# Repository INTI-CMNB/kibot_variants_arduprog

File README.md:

# KiBot variants example

This is an example of how to use variants with [KiBot](https://github.com/INTI-CMNB/KiBot).

## Index

* [Definition](#Definition)
* [Implementation](#Implementation)
* [Example](#Example)
* [**Results**](#Results)
  * [Schematic PDF](#Schematic-PDF)
  * [Bill of Materials](#Bill-of-Materials)
  * [PCB PDF](#PCB-PDF)
  * [Gerbers](#Gerbers)
  * [Position](#Position)
  * [3D Model](#3D-Model)
* [Changing values](#Changing-values)
* [A complete example](#A-complete-example)

# Definition

In the KiBot context a variant is what is usually known as an *assembly variant*.
So the idea is that you have **one** PCB, but various different *variants* (*flavors*) of the product.
The difference between them is which components are used.

Typical applications are:
- Optional functionality
- Support for different normatives
- Testing purposes

Currently KiBot can handle not only which components are soldered, but also different values.
The support for different values is complex and only used by a minority.
So please be patient if some use case isn't well covered, just report it.

# Implementation

To create a variant you must add specific fields to the components in the schematic.
Currently KiBot supports three methodes:

- **KiBoM style**: one field, usually named *Config*, contains information to include or exclude a component for one or more variants.
- **KiCost style**: one field assigns the component to one or more groups, you provide a regular expression to include certain groups.
- **IBoM style**: one field assigns the component to a group, you provide lists to exclude or include certain groups.

# Example

The best way to explain how to use it is using an example.
We start with an hypothetic design: the *programmer* section of the [Arduino UNO R3](https://content.arduino.cc/assets/UNO-TH_Rev3e_sch.pdf).
The schematic is the following:

This is basically an ATMega8U2 used as a bridge between USB and the Arduino UNO serial port.
So we will assume this board is useful. We'll also assume we have three possible uses:

- The full board with USB support. We'll name it **USB** variant.
- A version of the board that we want to use as a plain microcontroller. So we remove the USB. We'll name it **XTAL** variant.
- An even more modest version where we use the internal clock oscillator and we can remove the crystal. We'll name it **default** variant.

Additionally:

- In the USB version we want to remove the ICSP1 connector. We'll flash the CPU in-house and the user won't need to do it. ICPS1 will be solded for the other two variants.
- The J4 connector is completely optional. It won't be included in any variant.

The first step is to choose a variant mechanism. For this example we will use the [KiBoM](https://github.com/SchrodingersGat/KiBoM) style.
This style puts more information inside the schematic, so you need to provide less information from outside.

Now that we chose a format we must add the corresponding *tags*. We can identify four groups of components here:

- The USB components (J2, F1, R1, R2, RV1, RV2 and FB1). Used only for the **USB** variant.
- The ICSP1 connector (J5). Excluded from the **USB** variant.
- The crystal components (R3, Y1, C3, C4). Used only for the **USB** and **XTAL** variants.
- The 2x2M connector (J4). Never used.

To mark components that will be added to the board only for certain variant KiBoM uses **+VARIANT**.
And when we want to exclude a component from a variant we use **-VARIANT**.

We'll use the default *Config* field. So lets see what we'll use for each group.

- For the USB components we'll use **+USB** because these components will be used only for the **USB** variant.
- For the ICSP1 connector we'll use **-USB** because this component will be solded for all variants, except **USB**.
- Now the crystal stuff is a little bit more complex. We could use **+XTAL**, but then these components won't be included in the **USB** version.
  So what we use is **+USB,+XTAL** this makes the components available for both variants.
- The J4 case is handled in a different way. KiBoM filters removes any component mentioning the **DNF** word in the config. So we can just use it.

Now that we know what to use we'll add the *Config* field to the mentioned components.
To make it faster we can add it to one component, lets say to J4, and then use the *Tools -> Edit symbol fields* menu option.
Here is what we should have in the *Config* field:

This is all we need to add to the schematic. Now is time to configure KiBot.

If you don't know about the KiBot file format you could be interested in reading the following [explanation](https://github.com/INTI-CMNB/KiBot/blob/master/docs/KiPlotYAML.md).
YAML files are self explanatory, so perhaps you can go on even without knowing about the format.

Ok, now we have to define the three variants we mentioned before: **USB**, **XTAL** and **default**.
All variants will be put in a section named **variants**. So we'll create a list of items, each item is a variant definition.
Lets start with the simplest: **default**. Here is what we use:

```yaml
variants:
  - name: 'default'
    comment: 'Minimal PCB no USB'
    type: kibom
```

This is the section **variants** and its first item. The name is **default** and we added a comment to remmember what this variant is.
We also define the type as **kibom**, what we called *style*.

Now lets go for the second, here we add:

```yaml
  - name: 'USB'
    comment: 'Full board'
    type: kibom
    file_id: _USB
    variant: USB
```

You'll notice two new attributes: `file_id` and `variant`. The first is what we'll add to the names of the files in order to distinguish from the **default**.
And the second ... well this is just the *tag* we used to mark **USB** components.

You should be able to figure out how to define the third variant, here we go:

```yaml
  - name: 'XTAL'
    comment: 'No USB, but crystal included'
    type: kibom
    file_id: _XTAL
    variant: XTAL
```

A little bit long, but simple. Here is all together:

```yaml
variants:
  - name: 'default'
    comment: 'Minimal PCB no USB'
    type: kibom

  - name: 'USB'
    comment: 'Full board'
    type: kibom
    file_id: _USB
    variant: USB

  - name: 'XTAL'
    comment: 'No USB, but crystal included'
    type: kibom
    file_id: _XTAL
    variant: XTAL
```

This is all we need to define the variants. Of course our config file must define what to do with the variants.
But this document is about the variants, we won't focuse on the rest.
You can see the whole configuration file [here](ardu_prog.kibot.yaml).

What now? How can we tell KiBot what variant to use?
There are three methodes:

1. Use the `variant` option for an specific output.
2. Select a default variant to be used by all outputs that doesn't specify a variant.
3. Same as above but from the command line.

The simplest way is the third. In this case we just need to add `-g variant=NAME` to the command line.
Lets say we have a copy of the repo containing this example and we want to generate the BoM.
In our example the HTML BoM output is named `bom_html` so we can just run:

```bash
kibot -s run_erc,run_drc -d Result bom_html
```

This will create `Result/BoM/t1-bom.html`. To generate the BoM for the **USB** variant we can use:

```bash
kibot -s run_erc,run_drc -d USB -g variant=USB bom_html
```

And we'll get a different BoM in `USB/BoM/t1-bom_USB.html`.

The CI/CD workflow for this repo runs the ERC and DRC checks and then generates all the configured outputs for the three variants.
The commands used are approximately these:

```bash
kibot -d Generated -s run_drc -i
kibot -d Generated -s run_erc -i
kibot -d Generated/default -g variant=default -s run_erc,run_drc
kibot -d Generated/USB -g variant=USB -s run_erc,run_drc
kibot -d Generated/XTAL -g variant=XTAL -s run_erc,run_drc
```

The first two are the checks, no output generated. The other three skips the checks and generates all outputs for each variant.
All files are stored in the `Generated` folder.

# Results

Here is what we get, you can download the results obtained on GitHub CI/CD Actions from [here](https://github.com/INTI-CMNB/kibot_variants_arduprog/actions/runs/4584580459).
Click on the images to get a larger image or the generated document.

## Schematic PDF

Excluded components are marked with a cross:

- Default variant

- XTAL variant

- USB variant

## Bill of Materials

Excluded components are listed as DNF in a separated list. Note we could also remove them.

- Default variant

- XTAL variant

- USB variant

The XLSX files contain the same information, arranged a little bit different, here is the USB variant:

## PCB PDF

Excluded components are marked with a cross in the *.Fab layer. Their solder paste and adhesive glue is removed from *.Paste and *.Adhes.
The following PDFs were gnerated including F.Fab, F.Paste, F.Adhes and Dwgs.User:

- Default variant

- XTAL variant

- USB variant

## Gerbers

Excluded components are marked with a cross in the *.Fab layer. Their solder paste and adhesive glue is removed from *.Paste and *.Adhes:

- Default variant

- XTAL variant

- USB variant

## Position

Here only the fitted components are included in the pick and place file:

- Default variant
```
### Module positions - created on Thu 10 Sep 2020 20:10:57  ###
### Printed by KiBot
## Unit = mm, Angle = deg.
## Side : both
# Ref   Val                  Package                                     PosX       PosY       Rot        Side
C1     47uF                 CP_Elec_8x10                                130.8354   -94.8944   270.0000   top
C2     100nF                C_0805_2012Metric                           123.0000   -90.9000   0.0000     top
C5     1uF                  C_0805_2012Metric                           163.3220   -89.1540   270.0000   top
C6     100nF                C_0805_2012Metric                           162.3822   -82.0674   90.0000    top
C7     100nF                C_0805_2012Metric                           153.9748   -78.8670   0.0000     top
C8     100nF                C_0805_2012Metric                           144.7546   -78.9686   90.0000    top
D1     CD1206-S01575        D_1206_3216Metric                           162.8140   -96.7740   90.0000    top
D2     LED                  LED_0805_2012Metric                         147.3200   -74.9500   90.0000    top
D3     LED                  LED_0805_2012Metric                         144.7800   -74.9500   90.0000    top
J1     Barrel_Jack_Switch   BarrelJack_CLIFF_FC681465S_SMT_Horizontal   126.1000   -81.2000   0.0000     top
R4     10K                  R_0805_2012Metric                           159.0040   -95.7580   90.0000    top
R5     1K                   R_0805_2012Metric                           144.7546   -82.8040   270.0000   top
R6     1K                   R_0805_2012Metric                           147.3200   -70.1748   270.0000   top
R7     1K                   R_0805_2012Metric                           144.7800   -70.1748   270.0000   top
U1     ATmega8U2-AU         TQFP-32_7x7mm_P0.8mm                        154.4320   -85.8520   270.0000   top
## End
```
- XTAL variant
```
### Module positions - created on Thu 10 Sep 2020 20:11:59  ###
### Printed by KiBot
## Unit = mm, Angle = deg.
## Side : both
# Ref   Val                  Package                                     PosX       PosY       Rot        Side
C1     47uF                 CP_Elec_8x10                                130.8354   -94.8944   270.0000   top
C2     100nF                C_0805_2012Metric                           123.0000   -90.9000   0.0000     top
C3     22pF                 C_0805_2012Metric                           162.2600   -75.1160   270.0000   top
C4     22pF                 C_0805_2012Metric                           155.9100   -75.1160   270.0000   top
C5     1uF                  C_0805_2012Metric                           163.3220   -89.1540   270.0000   top
C6     100nF                C_0805_2012Metric                           162.3822   -82.0674   90.0000    top
C7     100nF                C_0805_2012Metric                           153.9748   -78.8670   0.0000     top
C8     100nF                C_0805_2012Metric                           144.7546   -78.9686   90.0000    top
D1     CD1206-S01575        D_1206_3216Metric                           162.8140   -96.7740   90.0000    top
D2     LED                  LED_0805_2012Metric                         147.3200   -74.9500   90.0000    top
D3     LED                  LED_0805_2012Metric                         144.7800   -74.9500   90.0000    top
J1     Barrel_Jack_Switch   BarrelJack_CLIFF_FC681465S_SMT_Horizontal   126.1000   -81.2000   0.0000     top
R3     1M                   R_0805_2012Metric                           158.9580   -75.8780   180.0000   top
R4     10K                  R_0805_2012Metric                           159.0040   -95.7580   90.0000    top
R5     1K                   R_0805_2012Metric                           144.7546   -82.8040   270.0000   top
R6     1K                   R_0805_2012Metric                           147.3200   -70.1748   270.0000   top
R7     1K                   R_0805_2012Metric                           144.7800   -70.1748   270.0000   top
U1     ATmega8U2-AU         TQFP-32_7x7mm_P0.8mm                        154.4320   -85.8520   270.0000   top
Y1     16MHz                Crystal_SMD_Abracon_ABM3-2Pin_5.0x3.2mm     158.9278   -70.0278   180.0000   top
## End
```
- USB variant
```
### Module positions - created on Thu 10 Sep 2020 20:11:27  ###
### Printed by KiBot
## Unit = mm, Angle = deg.
## Side : both
# Ref   Val                  Package                                     PosX       PosY       Rot        Side
C1      47uF                 CP_Elec_8x10                                130.8354   -94.8944   270.0000   top
C2      100nF                C_0805_2012Metric                           123.0000   -90.9000   0.0000     top
C3      22pF                 C_0805_2012Metric                           162.2600   -75.1160   270.0000   top
C4      22pF                 C_0805_2012Metric                           155.9100   -75.1160   270.0000   top
C5      1uF                  C_0805_2012Metric                           163.3220   -89.1540   270.0000   top
C6      100nF                C_0805_2012Metric                           162.3822   -82.0674   90.0000    top
C7      100nF                C_0805_2012Metric                           153.9748   -78.8670   0.0000     top
C8      100nF                C_0805_2012Metric                           144.7546   -78.9686   90.0000    top
D1      CD1206-S01575        D_1206_3216Metric                           162.8140   -96.7740   90.0000    top
D2      LED                  LED_0805_2012Metric                         147.3200   -74.9500   90.0000    top
D3      LED                  LED_0805_2012Metric                         144.7800   -74.9500   90.0000    top
F1      MF-MSMF050-2         R_1812_4532Metric                           167.8940   -77.2160   0.0000     top
FB1     BLM21PG221SN1D       R_0805_2012Metric                           167.8940   -90.6780   180.0000   top
J1      Barrel_Jack_Switch   BarrelJack_CLIFF_FC681465S_SMT_Horizontal   126.1000   -81.2000   0.0000     top
R1      22R                  R_0805_2012Metric                           166.3700   -86.1060   0.0000     top
R2      22R                  R_0805_2012Metric                           166.3700   -83.8200   0.0000     top
R3      1M                   R_0805_2012Metric                           158.9580   -75.8780   180.0000   top
R4      10K                  R_0805_2012Metric                           159.0040   -95.7580   90.0000    top
R5      1K                   R_0805_2012Metric                           144.7546   -82.8040   270.0000   top
R6      1K                   R_0805_2012Metric                           147.3200   -70.1748   270.0000   top
R7      1K                   R_0805_2012Metric                           144.7800   -70.1748   270.0000   top
RV1     CG0603MLC-05E        R_0603_1608Metric                           170.4340   -87.3505   270.0000   top
RV2     CG0603MLC-05E        R_0603_1608Metric                           170.4340   -82.3214   90.0000    top
U1      ATmega8U2-AU         TQFP-32_7x7mm_P0.8mm                        154.4320   -85.8520   270.0000   top
Y1      16MHz                Crystal_SMD_Abracon_ABM3-2Pin_5.0x3.2mm     158.9278   -70.0278   180.0000   top
## End
```

## 3D Model

Excluded components are removed from the 3D model (STEP file, 3D Viewer render and Blender export):

- Default variant (click to enlarge)

- XTAL variant (click to enlarge)

- USB variant (click to enlarge)

# Changing values

Variants can also affect any of the component fields. In order to overwrite one field value when a variant is selected you must define a field named `VARIANT:FIELD`.
The value for this field will replace the value of the regular `FIELD` when the `VARIANT` is in use.

Here is an example, if you have a resistor with a value of 1k and you want this value to change to 2k2 when the `test` variant is in use you just need to define a field named `test:value` and assign `2k2` to this field.

To enable it you just need to add a `pre_transform` filter of the type `var_rename` to the variant performing the transformation. Suppose you have the following variants:

```yaml
variants:
  - name: 'production'
    comment: 'Production variant'
    type: kibom
    file_id: '_(PROD)'
    variant: PROD

  - name: 'development'
    comment: 'Development variant'
    type: kibom
    file_id: '_(DEV)'
    variant: DEV
```

And you want to both apply such a transformation you can define:

```yaml
filters:
  - name: 'Variant rename'
    type: var_rename
    separator: ':'
    variant_to_value: true

variants:
  - name: 'production'
    comment: 'Production variant'
    type: kibom
    file_id: '_(PROD)'
    variant: PROD
    pre_transform: 'Variant rename'

  - name: 'development'
    comment: 'Development variant'
    type: kibom
    file_id: '_(DEV)'
    variant: DEV
    pre_transform: 'Variant rename'
```

The `separator` option controls which character is used to separate the `VARIANT` and the `FIELD` in the field name.

The `variant_to_value` enables the conversion from fields named `VARIANT` to the component value when the variant is in use.

To make things simpler you can use an internally defined filter called `_var_rename`. This is a `var_rename` filter with `:` as separator and `variant_to_value` disabled. Using it the configuration is simpler:

```yaml
variants:
  - name: 'production'
    comment: 'Production variant'
    type: kibom
    file_id: '_(PROD)'
    variant: PROD
    pre_transform: '_var_rename'

  - name: 'development'
    comment: 'Development variant'
    type: kibom
    file_id: '_(DEV)'
    variant: DEV
    pre_transform: '_var_rename'
```

# A complete example

The configuration file used in this example can be found [here](https://github.com/INTI-CMNB/kibot_variants_arduprog/blob/master/ardu_prog.kibot.yaml).

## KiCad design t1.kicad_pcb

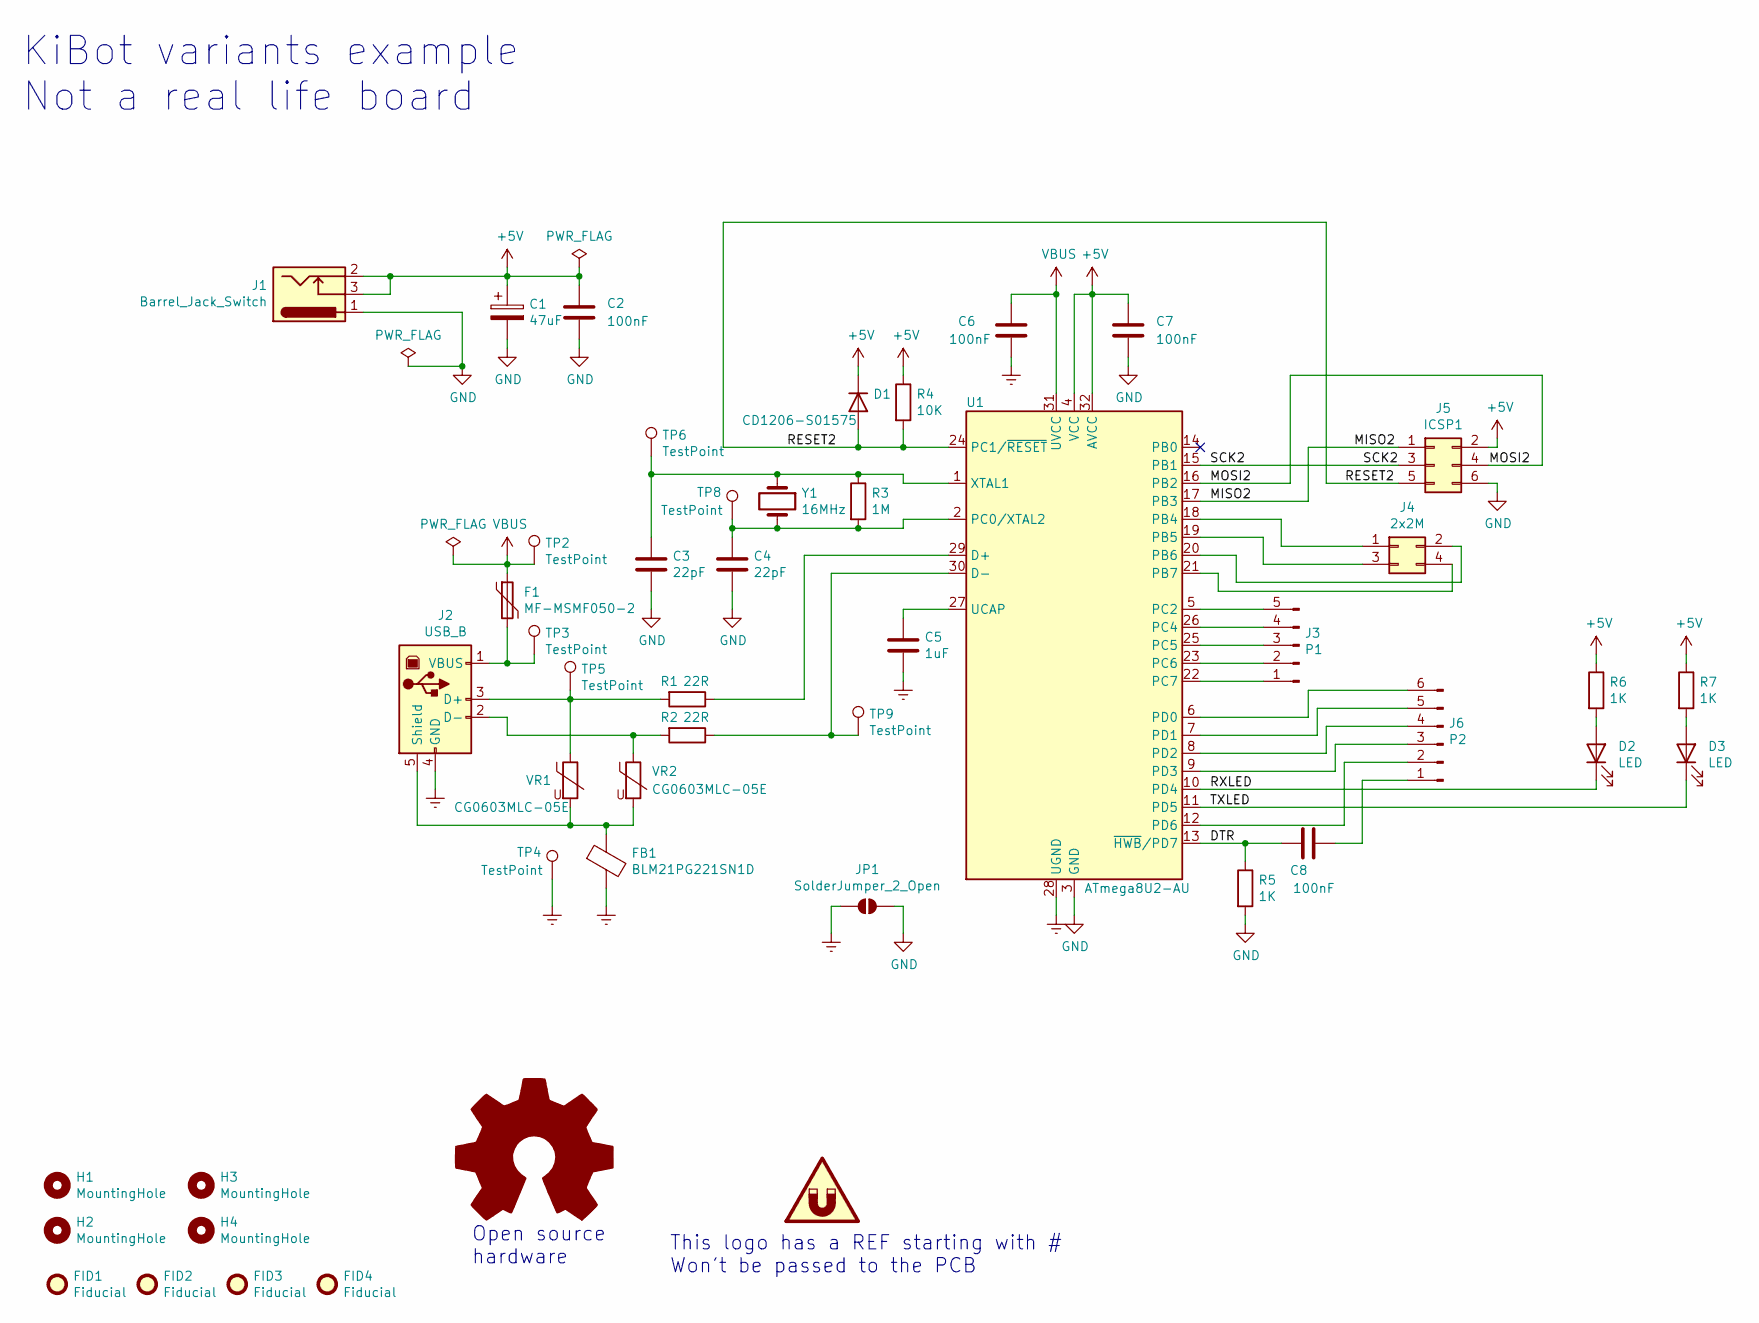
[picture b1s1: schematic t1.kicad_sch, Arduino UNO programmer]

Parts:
C1: 47uF; CP_Elec_8x10
C2, C6, C7, C8: 100nF; C_0805_2012Metric
C3, C4: 22pF; C_0805_2012Metric
C5: 1uF; C_0805_2012Metric
D1: CD1206-S01575; D_1206_3216Metric
D2, D3: LED; LED_0805_2012Metric
F1: MF-MSMF050-2; R_1812_4532Metric
FB1: BLM21PG221SN1D; R_0805_2012Metric
FID1, FID2, FID3, FID4: Fiducial; Fiducial_0.75mm_Mask1.5mm
H1, H2, H3, H4: MountingHole; MountingHole_2.7mm_M2.5
J1: Barrel_Jack_Switch; BarrelJack_CLIFF_FC681465S_SMT_Horizontal
J2: USB_B; USB_B_Lumberg_2411_02_Horizontal
J3: P1; PinHeader_1x05_P2.54mm_Vertical
J4: 2x2M; PinHeader_2x02_P2.54mm_Vertical
J5: ICSP1; PinHeader_2x03_P2.54mm_Vertical
J6: P2; PinHeader_1x06_P2.54mm_Vertical
JP1: SolderJumper_2_Open; SolderJumper-2_P1.3mm_Open_RoundedPad1.0x1.5mm
LOGO1: Logo_Open_Hardware_Large; OSHW-Logo_11.4x12mm_SilkScreen
R1, R2: 22R; R_0805_2012Metric
R3: 1M; R_0805_2012Metric
R4: 10K; R_0805_2012Metric
R5, R6, R7: 1K; R_0805_2012Metric
TP2, TP3, TP4, TP5, TP6, TP8, TP9: TestPoint; TestPoint_Pad_D1.0mm
U1: ATmega8U2-AU; TQFP-32_7x7mm_P0.8mm
VR1, VR2: CG0603MLC-05E; R_0603_1608Metric
Y1: 16MHz; Crystal_SMD_Abracon_ABM3-2Pin_5.0x3.2mm

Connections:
+5V: C1.1, C2.1, C7.1, D1.1 (K), J1.2, J1.3, J5.2, R4.1, R6.1, R7.1, U1.4 (VCC), U1.32 (AVCC)
/DTR: C8.1, R5.1, U1.13 (~HWB/PD7)
/MISO2: J5.1, U1.17 (PB3)
/MOSI2: J5.4, U1.16 (PB2)
/RESET2: D1.2 (A), J5.5, R4.2, U1.24 (PC1/~RESET)
/RXLED: D2.1 (K), U1.10 (PD4)
/SCK2: J5.3, U1.15 (PB1)
/TXLED: D3.1 (K), U1.11 (PD5)
Earth: C5.2, C6.2, FB1.2, J2.4 (GND), JP1.1 (A), TP4.1, U1.28 (UGND)
GND: C1.2, C2.2, C3.2, C4.2, C7.2, J1.1, J5.6, JP1.2 (B), R5.2, U1.3 (GND)
unnamed: D2.2 (A), R6.2
unnamed: D3.2 (A), R7.2
unnamed: J2.3 (D+), R1.2, TP5.1, VR1.1
unnamed: J2.2 (D-), R2.2, VR2.1
unnamed: FB1.1, J2.5 (Shield), VR1.2, VR2.2
unnamed: F1.2, J2.1 (VBUS), TP3.1
unnamed: J3.1, U1.22 (PC7)
unnamed: J3.2, U1.23 (PC6)
unnamed: J3.3, U1.25 (PC5)
unnamed: J3.4, U1.26 (PC4)
unnamed: J3.5, U1.5 (PC2)
unnamed: J4.1, U1.18 (PB4)
unnamed: J4.2, U1.20 (PB6)
unnamed: J4.3, U1.19 (PB5)
unnamed: J4.4, U1.21 (PB7)
unnamed: C8.2, J6.1
unnamed: J6.2, U1.12 (PD6)
unnamed: J6.3, U1.9 (PD3)
unnamed: J6.4, U1.8 (PD2)
unnamed: J6.5, U1.7 (PD1)
unnamed: J6.6, U1.6 (PD0)
unnamed: R1.1, U1.29 (D+)
unnamed: R2.1, TP9.1, U1.30 (D-)
unnamed: C4.1, R3.2, TP8.1, U1.2 (PC0/XTAL2), Y1.2
unnamed: C5.1, U1.27 (UCAP)
unnamed: C3.1, R3.1, TP6.1, U1.1 (XTAL1), Y1.1
VBUS: C6.1, F1.1, TP2.1, U1.31 (UVCC)

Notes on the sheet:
Open source hardware
This logo has a REF starting with # Won't be passed to the PCB
KiBot variants example Not a real life board

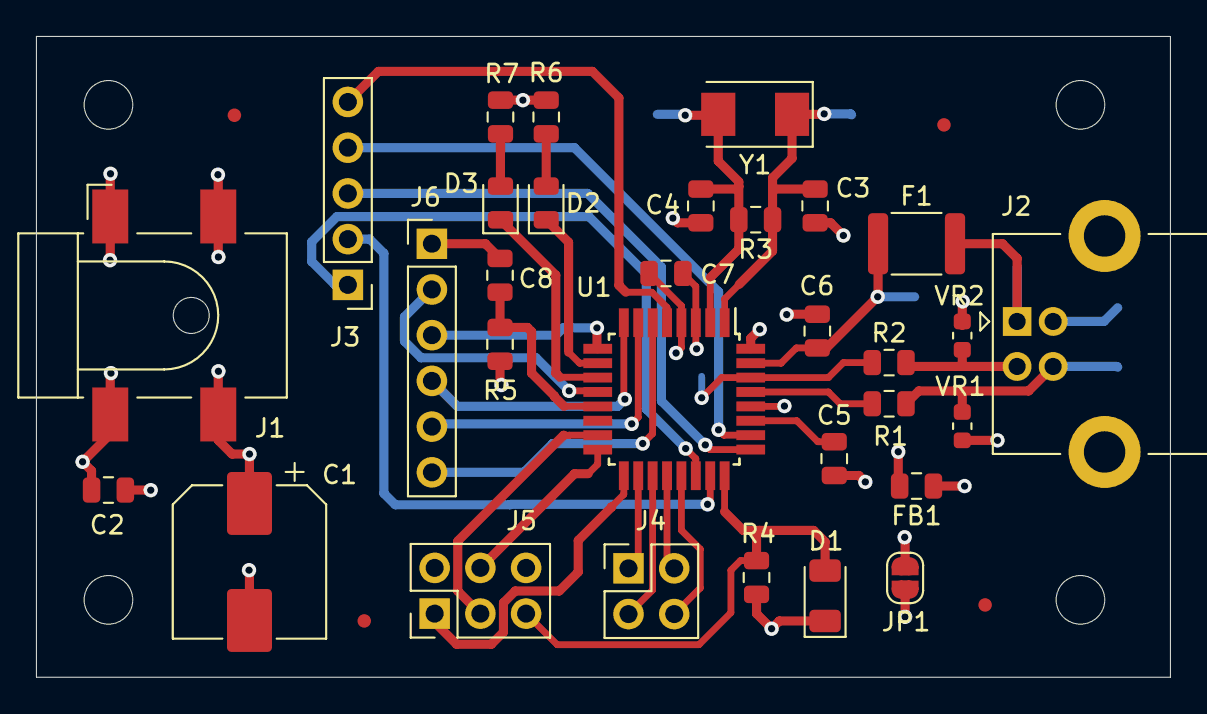
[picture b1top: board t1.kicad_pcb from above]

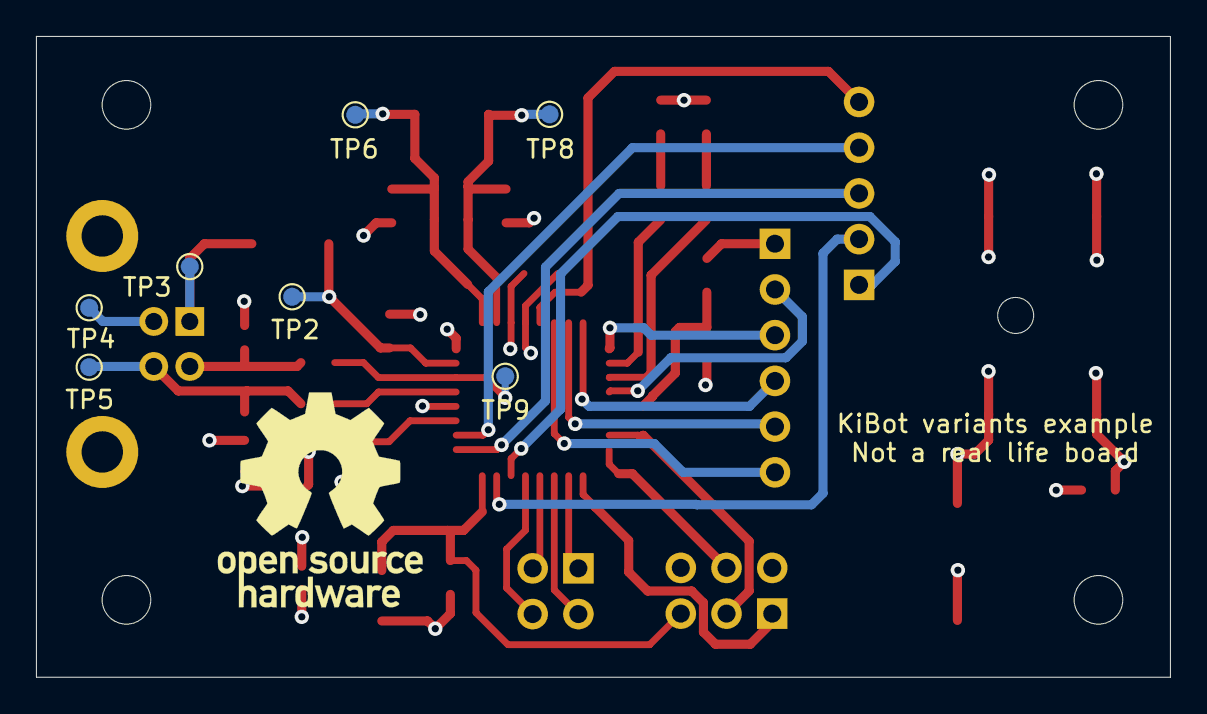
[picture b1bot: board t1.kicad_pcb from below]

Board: 4 copper layers, 63.0 x 35.6 mm, 47 parts (8 on the bottom side), 37 nets.

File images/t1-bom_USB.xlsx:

|  | KiBot variants example
 |  | Schematic: | t1 | Component Groups: | 21
 |  | Variant: | USB | Component Count: | 30
 |  | Revision: | r1 | Fitted Components: | 28
 |  | Date: | 2020-09-09 | Number of PCBs: | 1
 |  | KiCad Version: | 5.1.6+dfsg1-1~bpo10+1 | Total Components: | 28
Row | References | Quantity Per PCB | Value | Manufacturer | Manf. Part | Footprint
1 | C3 C4 | 2 | 22 pF |  |  | C_0805_2012Metric
2 | C2 C6 C7 C8 | 4 | 100 nF |  |  | C_0805_2012Metric
3 | C5 | 1 | 1 µF |  |  | C_0805_2012Metric
4 | C1 | 1 | 47 µF | Vishay Beyschlag/Draloric/BC Components | MAL215371479E3 | CP_Elec_8x10
5 | D1 | 1 | CD1206-S01575 |  |  | D_1206_3216Metric
6 | D2 D3 | 2 | LED | OSRAM Opto Semiconductors Inc. | LG R971-KN-1 | LED_0805_2012Metric
7 | F1 | 1 | MF-MSMF050-2 |  |  | R_1812_4532Metric
8 | FB1 | 1 | BLM21PG221SN1D | Murata | BLM21PG221SN1D | R_0805_2012Metric
9 | J1 | 1 | Barrel_Jack_Switch | Würth Elektronik | 694106106102 | BarrelJack_CLIFF_FC681465S_SMT_Horizontal
10 | J3 | 1 | P1 |  |  | PinHeader_1x05_P2.54mm_Vertical
11 | J6 | 1 | P2 |  |  | PinHeader_1x06_P2.54mm_Vertical
12 | J2 | 1 | USB_B | TE Connectivity AMP Connectors | 292304-1 | USB_B_Lumberg_2411_02_Horizontal
13 | R1 R2 | 2 | 22 Ω |  |  | R_0805_2012Metric
14 | R5 R6 R7 | 3 | 1 kΩ |  |  | R_0805_2012Metric
15 | R4 | 1 | 10 kΩ |  |  | R_0805_2012Metric
16 | R3 | 1 | 1 MΩ |  |  | R_0805_2012Metric
17 | RV1 RV2 | 2 | CG0603MLC-05E | Bourns Inc. | CG0603MLC-05E | R_0603_1608Metric
18 | U1 | 1 | ATmega8U2-AU |  |  | TQFP-32_7x7mm_P0.8mm
19 | Y1 | 1 | 16MHz | Abracon LLC | ABM3-16.000MHZ-B2-T | Crystal_SMD_Abracon_ABM3-2Pin_5.0x3.2mm

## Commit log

2020-09-10 Added the schematic and PCB
2020-09-10 Added all the 3D models used to this project.
2020-09-10 Added workflow to generate all data
2020-09-10 Added files needed for data generation
2020-09-10 Removed time command use, not in docker image.
2020-09-10 Added introduction and schematic
2020-09-10 Added snapshot of the Symbol Fields dialog.
2020-09-10 Added resulting schematic
2020-09-10 Added BoMs
2020-09-10 Switched to GitHub Pages.
2020-09-10 More changes to pages
2020-09-11 Added one XLSX examples.
2020-09-11 Added gerber images
2020-09-11 Added pick & place files.
2020-09-11 Changed position URLs to point to Git Pages
2020-09-11 Experimented with embedded .pos
2020-09-11 Added STEP images
2020-09-11 Added missing STEP images.
2020-09-11 Testing better index
2020-09-11 Trying with - instead of space
2020-09-11 Added more index entries
2020-09-11 Fixed links
2020-09-11 Experimenting with better title for images.
2020-09-11 Better image titles
2020-09-11 Added variable to make it easier to run a local copy of kibot
2020-09-11 Added a PDF output with F.Fab, F.Paste and F.Adhes.
2020-09-11 Added PCB PDF examples.
2020-09-11 Fixed USB <-> XTAL in PCB PDF section
2020-09-11 Excluded the Generated dir.
2020-09-11 Small fixes and additions.
2020-09-11 Set theme jekyll-theme-leap-day
2020-09-11 Added a logo that reflects the idea.
2020-09-11 Fixed cropped orange points
2020-09-12 Changed the web page title.
2020-09-12 Trying to make better use of the width.
2020-09-12 Trying width in another file
2020-09-12 Another try with the width
2020-09-12 Adjust nav width
2020-09-12 Page sizes adjust
2020-12-23 Added variant field renamer explanation.
2021-11-11 Fixed Makefile (erc <-> drc) (Fixes #1)
2021-11-11 Set KIBOT conditionnally in Makefile
    On windows, I used a [wrapper script](https://github.com/INTI-CMNB/kicad_auto/issues/5#issue-1051018841~ ) to launch kicost in docker.
    Setting KIBOT conditionnally allows the environment variable KIBOT to be applied without having to set the '-e' option for make
2021-11-11 Change to upload-artifact@v2 because v1 is missing required runs.using When running act, the error was revealed. Solution suggested for another action at https://github.com/nektos/act/issues/322 http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
2021-11-12 Added 2D image generation with components
2021-11-15 [Makefile] Allowed to overwrite the KIBOT var
2022-02-24 Added link to YAML config
2022-03-25 Added a GitHub action test
2022-03-25 Added options to the action
2022-03-25 Changed the names of the workflows
    - Made them different and more descriptive
2022-03-25 Implemented variants in the GitHub action
2022-03-25 Fixed ERC <-> DRC in the Makefile
2022-03-25 Separated ERC/DRC in the GitHub actions example
2022-03-25 Removed unneeded `config` in GitHub action example.
2022-03-25 Test for unified KiCad GitHub action
2022-03-25 Second test for unified KiCad action
2022-03-25 Third test to unify KiCad
2022-03-25 4th try tounify KiCad
2022-03-25 5th try to unify
2022-03-25 Gave-up trying to unify both images, GitHub is too limited.
2022-03-29 Migrated to KiCad 6.
2022-03-29 Updated symbols to the ones currently used by KiCad
2022-03-29 Removed unused track
2022-03-29 Renamed varistors from RV to VR (not potentiometers)
2022-03-29 Added filter for DRC errors about silk text outside board.
2022-03-29 Also renamed varistors in the PCB
2022-03-29 Exclude t1.xml, is generated by KiBot
2022-03-29 Added XML netlist generation (can help iBoM)
2022-03-29 Removed `show_components: all` from pcbdraw
    - We are filtering them with variants
2022-03-29 Separated variants in different targets and added target for XML
2022-03-29 Switched workflows to KiCad 6
2022-03-29 Switched to dev_k6 image
2022-03-29 Added 3D render example
2022-03-29 Updated 3D images using 3D Viewer render
2022-04-18 Adapted the example to `pcb_print`
    - Nicer output
    - Example of custom worksheet
    - Example of git hash in revision
2022-05-01 Added --quick-start workflow example
2022-05-02 Fixed quick-start workflow name
2022-05-02 Added test for GitHub action with quick-start
2022-05-02 Trying to debug the quick-start option
2022-05-02 Another try to quick-start
2022-05-02 Switched quick-start example to v2_k6 tag
2022-06-14 Added navigate results deployment
    - To INTI-CMNB/kibot_variants_arduprog_site@main
2022-06-21 Trigger github action workflow
2022-07-13 [GitHub Action workflow] Adjusted the comments
2022-07-13 Trigger GitHub Action v1 rebuild
2022-07-13 [GitHub Action] Added test for v1 with KiCad 6
2022-07-13 [GitHub Action] Fixed schematics extension
2022-07-13 [GitHub Action] Trigger build
2022-07-13 [GitHub Action v2_1_2_0] Added test for this tag
2022-07-13 [GitHub Action v2_1_2_0] Fixed board and schematic spec
2022-07-13 [GitHub Action v2_k6_1_2_0] Added test for this action tag
2022-07-13 [GitHub Action v2_k6] Removed wrong comment on workflow
2022-09-27 Changed to use GitHub kicad6_auto image
2022-09-27 Changed Quick-Start example to use GH images
2022-09-27 Updated BLM21PG221SN1 datasheet
2022-09-27 Fixed triggers to use kicad_sch (not sch)
2022-09-27 Now we checkout the whole repo, not just the las commit to get a diff
2022-09-27 Changed Quick Start example to use full image
    - Also moved the site upload to the image (not action)
2022-09-27 Fixed the deploy mechanism
    - We need to run it on the plain Ubuntu, the kicad_auto image doesn't
    contain rsync
2022-09-27 Fixed steps dependency
2022-09-27 Added path to download-artifact
2022-09-27 And also needs the repo ...
2022-09-28 Testing changes in the GitHub Action
    - Pulling docker image from GH registry
2022-09-28 Reverted the GitHub Action test
    - Was successful
2022-10-17 [CI/CD] Added trigger for the GHA example
2022-10-21 [Test] Testing the quick start using dev images
    - To check the SVGs generated by SVG output
    - Now should work for browsers
2022-10-21 [Test] No full dev images, testing the normal ones
2022-10-21 [CI/CD] Added trigger to the quick start demo
2022-10-21 [Test] Reverting to full image
    - Successful test: SVGs are fixed in dev branch
2022-12-22 [DOCs] Removed the *experimental* status for the value variants
    - Now is more clear
2023-01-20 Better 3D models
    - Missing WRL files
2023-01-27 Added trigger for GHA + quick-start
2023-01-27 GHA example: upgraded checkout and uploadartifacts
2023-01-27 Switched v2_k6 to v2_dk6 for the quick-start example
    - v1.5.1 creates some files with 0600 permissions
2023-01-27 [GHA] Removed "kicad: 5", never implemented
2023-03-31 Made more clear the pre skip
    - Avoiding skip of things like text variables
2023-03-31 Adjusts to the kibot workflow
    - Switched to full image (Blender support)
    - Updated actions versions
    - Generate the variants in parallel
2023-03-31 Fixes to the KiBot config
    - Use of `output_id`
    - At least try to add the components for the filled PcbDraw outs
    - Added Blender render
2023-03-31 Replaced the images using Blender renders
2023-03-31 Added "click to enlarge"
2023-03-31 Fixed use of "-s all"
2023-03-31 Removed netlist generation, not needed
2023-03-31 Filtered known warnings
2023-03-31 Added project restore
2023-03-31 Added trigger for regular workflow
2023-03-31 Fixed skip: all in the GitHub action example
2023-04-01 Added banner to makefile
2023-04-01 Ignore back-ups and cache
2023-04-01 Lib cache no longer needed
2023-04-01 Ignore lib_symbol_issues
    - Fully broken for this file
2023-04-01 Switching to dev images
2023-04-01 Added file log
2023-04-01 Removed the Makefile as trigger for the GHA
2023-04-01 Changed the board rotation in Blender to catch more light
2023-04-01 New images for the PCB (different rotation)
2023-04-01 Updated the README
    - Added KiCost variants
    - Updated artifacts URL
    - Added mention of Blender Export
2023-04-01 Better PCB print
2023-04-01 Removed YAML from GHA + QS
2023-04-01 Added variant to the PCB print title
2023-04-01 Updated the PCB Print outputs
2023-04-02 More coherence between schematic and PCB
    - Same time format, using the generation time stamp
    - Same title, adding the variant
    - Same worksheet. Why KiCad 6 doesn't respect the first page in the PCB?
    - Same revision, short git hash
2023-04-02 Updated the plain schematic image
2024-02-06 Disable Jekyll in the quick start web pages
    It removes KiRi folders
2024-02-06 Migrated to KiCad 7
    Also introduced some changes to get diffs
2024-02-06 Migrated workflows
    - To KiCad 7
    - To v4 versions (Node.js 16 deprecation)
2024-02-06 Fixed KiCad 7 DRC issues
2024-03-31 Migrating to KiCad 8
2024-03-31 Fixed deploy action version
2024-04-11 Fixed PCB parity
2024-04-11 Fixed ERC issues
    - Connector names changed from Male to Pin (OMG!)
    - Updated power components from KiCad 8 lib
    - Synzed the PCB
2024-10-01 Renamed MFN -> MNF and MFP -> MPN
    KiCost compatibility
2024-10-05 [CI/CD] Force artifact upload for kibot_action_quick_start.yml
2024-10-05 [CI/CD] Testing fix for the ExportProject template
2024-10-29 Moving the GHA quick-start to use the release (not dev)
2025-03-18 [CI/CD][Added] Pre-release test
2025-03-18 Migrated to KiCad 9 for tests
2025-03-18 [CI/CD] Migrated workflows to KiCad 9
